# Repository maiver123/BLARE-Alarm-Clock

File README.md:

# BLARE Alarm Clock

## About
A custom alarm clock project built around the Seeed Studio XIAO ESP32-C3.

## Project Structure
- `PCB/` — KiCad project files, schematic and PCB layout.
- `Production/` — Gerber and drill files for PCB manufacturing.
- `CAD/` — 3D model of the clock case and assembly.
- `Firmware/` — Alarm clock source code.

## Design Images
- Overall clock: To be added
- Schematic: To be added
- PCB layout: To be added
- Case assembly: To be added

## Bill of Materials
To be completed.

## Project Status
PCB layout and production files have been prepared. CAD and firmware are still to be completed.

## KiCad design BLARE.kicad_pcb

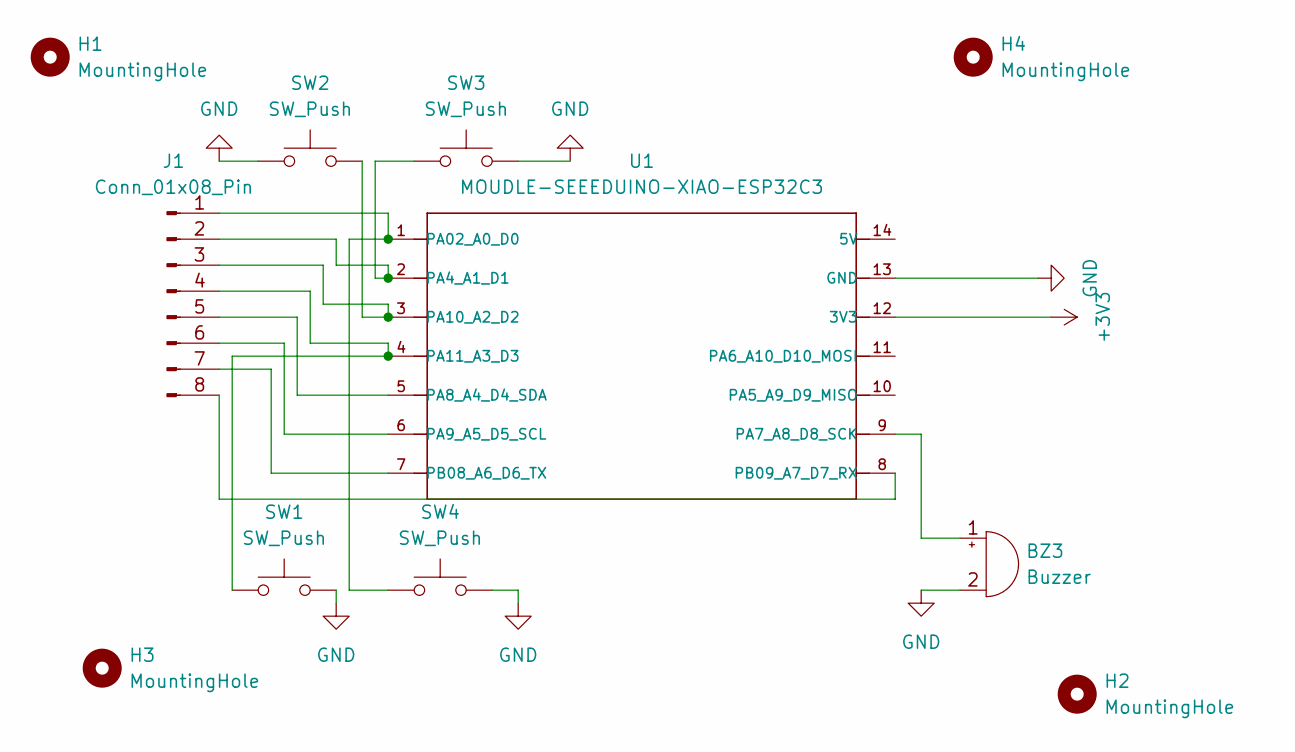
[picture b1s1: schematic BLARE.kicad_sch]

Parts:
BZ3: Buzzer; Buzzer_12x9.5RM7.6
H1, H2, H3, H4: MountingHole; MountingHole_3.2mm_M3
J1: Conn_01x08_Pin; PinHeader_1x08_P2.54mm_Vertical
SW1, SW2, SW3, SW4: SW_Push; SW_PUSH_1P1T_6x3.5mm_H4.3_APEM_MJTP1243
U1: MOUDLE-SEEEDUINO-XIAO-ESP32C3; MOUDLE14P-SMD-2.54-21X17.8MM

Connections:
+3V3: U1.12 (3V3)
GND: BZ3.2 (-), SW1.2, SW2.1, SW3.2, SW4.2, U1.13 (GND)
unnamed: BZ3.1 (+), U1.9 (PA7_A8_D8_SCK)
unnamed: J1.1, SW4.1, U1.1 (PA02_A0_D0)
unnamed: J1.2, SW3.1, U1.2 (PA4_A1_D1)
unnamed: J1.3, SW2.2, U1.3 (PA10_A2_D2)
unnamed: J1.4, SW1.1, U1.4 (PA11_A3_D3)
unnamed: J1.5, U1.5 (PA8_A4_D4_SDA)
unnamed: J1.6, U1.6 (PA9_A5_D5_SCL)
unnamed: J1.7, U1.7 (PB08_A6_D6_TX)
unnamed: J1.8, U1.8 (PB09_A7_D7_RX)

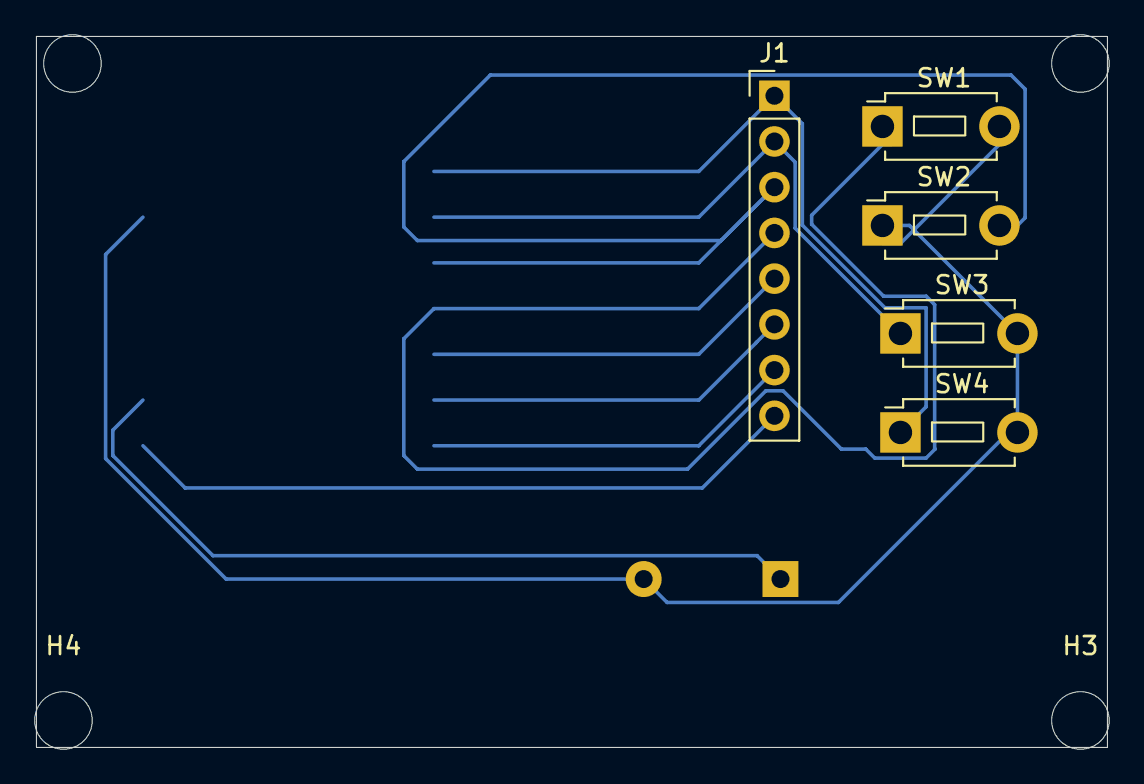
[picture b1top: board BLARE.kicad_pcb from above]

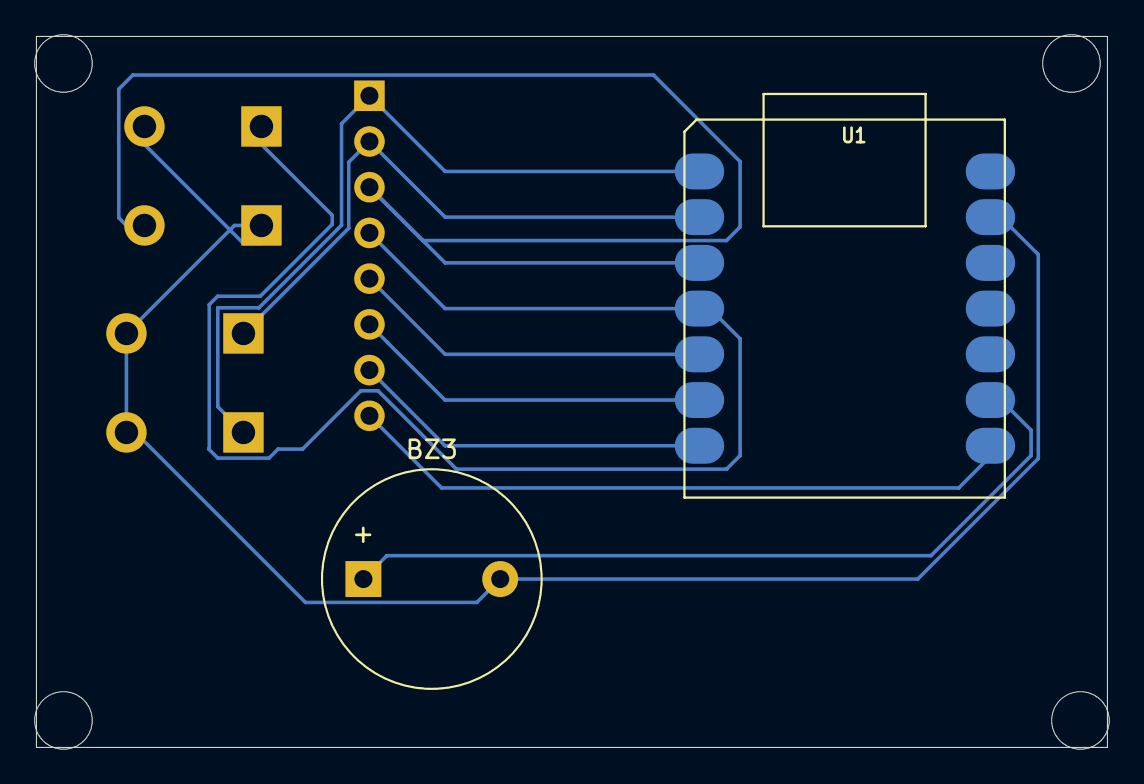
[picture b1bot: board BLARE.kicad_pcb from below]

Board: 2 copper layers, 59.5 x 39.5 mm, 11 parts (2 on the bottom side), 10 nets.
